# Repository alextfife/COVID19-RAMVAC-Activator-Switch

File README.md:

# COVID-AirLock

# NOTICE: There has been an issue with the tracing on these, will update once testing has been done. Transfering from kiCAD to EasyEDA removed some traces. 

Dental Office Air Filter Printed Circuit Board (PCB) Activation Switch. Inspired by the events of COVID-19.
This is a modification of a system Designed by RAMVAC Dental Vacuum System. 

<h2>Where did this come from?</h2>
A small minority of dental offices peppered around the United States in the early 2000's installed similar systems within their buildings that allow for air filtration per room, and in most cases, per 'area'. That is, it would be an inlet with 3 walls but no door, thus no closed in air source. Due to bad breath, debris from dental procedures, and sick patients, these filters were installed. 
Although its been roughly 20 years, this practice is not standard, or very popular. However that popularity is rising.

This filtration system is based almost completely on the saw dust collection filters that are installed at sawmills. However at a sawmill the power cost is astronomical due to all the vacuums being on for older systems. Newer systems use switches to activate which vacuum tubes receive suction, and to power on the vacuum.

<br>
Interestingly enough, RAMVAC produces their own switches for their current system. Theres however uses 4x the Wattage mine does. Unfortunately, my switches do not have LED's installed in the switch. 
Check theres out here: https://www.dentalez.com/product/remote-switch-panel/ 

During the COVID-19 pandemic of 2020-present, many dental offices are trying to implement this system now. 

<h2>So what is this project?</h2>
This github page is the evolution of the activator switch. The switch uses a sinusoidal signal to activate both the room's individual vacuum, and to open the aperature for that 'room's tube. 

This project is the creation of a wired switch that is more power efficient and cost efficient to produce than buy from the manufacture. 

<h2>Design Evolution</h2>
The switches are not my original design. The original design is without a patent. 
<h3>Some issues with the old, 'prototype' design. </h3>
<ol><li>It took AA batteries</li>
<li>The batteries corroded a lot and most units were switched out or bricks</li>
<li>The board itself had no seal or protection for components, and the copper on many of them was oxidizing.</li>
<li>There is no way to know when the switch had power or was dead until you took apart the switch socket.</li>
<li>The board itself is wider (by a small margin) than the footprint of the switch itself.</li>
</ol>

<h3>Design Evolution</h3>
The original design. None of this was of my doing.

With this, first thing I wanted to do was get rid of the batteries and do basic circuit analysis. 

<!--After downloading open source models of the parts I needed, I had created this. <br>
<br>-->

<br>
After checking PCB standards and compliance with the manufacturers, this was my first batch. I planned to save some money and solder them myself. <br>

<br>
Solding such small parts, and not having the funds for a microsolder meant I needed to tweak my design and send it to get fabricated and have the parts soldered on at the manufacturer. <br>
<!----><br>
To interface with the room like the old boards did, then I modified USB cables and was able to get them 5Vin as to not burn my boards.<br>
<br>

<h2>How to use it?</h2>
<h3>Connections</h3>
The boards are plugged in to the wall via USB adapter to any outlet. Therefore, you can hot switch the system around. <br>
<!---->

<br>
"Output" as seen on the board sends the signal from the board to a 2 pin terminal hardwired into the room. The "Switch" I/O on the board is where the USB power comes from. 
<h3>Usage</h3>
<br>
<i>Pictured: Dr. Robinette using vacuum tube after being activated.</i><br>
To use the airlocking vacuum system, one must simply turn it on and wait for about 10 seconds for the vacuum to charge to full sucking capacity. Then simply direct the tube to the patients breathing aperatures as shown below.<br>

<h2>Where is this?</h2>
My work as seen here is implemented at Gulf Coast Dental, in Bluewater Bay, FL. Please visit the website that I also designed! https://gulfcoastdental.com 

<br>
<i>I had express permission to photograph healthcare professionals and patients pictured to be in this documentation</i><br>

<h2>Do you want this?</h2> 
Please contact me, and I will promplty get in touch with you! 

I offered my design to the parent companyand I also applied for a position as product development engineer. I was rejected for the position. 

Under fair use, I have attached all designs and files to this repo for the unicorns out there whom this project might benefit!

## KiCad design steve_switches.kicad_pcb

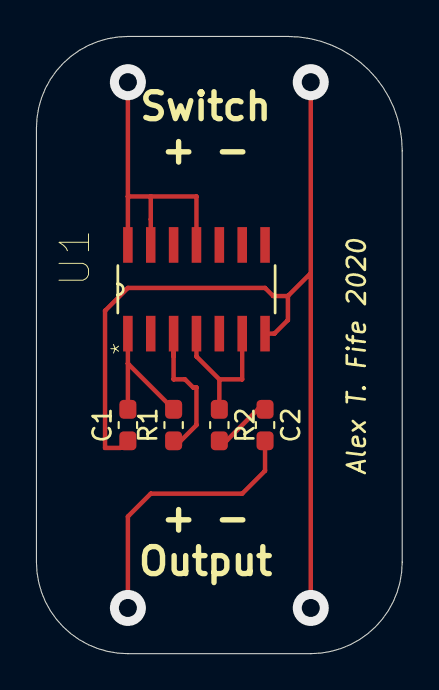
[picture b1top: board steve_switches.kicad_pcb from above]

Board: 2 copper layers, 20.3 x 34.3 mm, 5 parts (0 on the bottom side), 6 nets.

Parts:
C1: 1nF; C_0603_1608Metric_Pad1.05x0.95mm_HandSolder
C2: 120nF; C_0603_1608Metric_Pad1.05x0.95mm_HandSolder
R1: 1M; R_0603_1608Metric_Pad1.05x0.95mm_HandSolder
R2: 10k; R_0603_1608Metric_Pad1.05x0.95mm_HandSolder
U1: MC14106BDG; SOIC127P600X175-14N

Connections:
+3.3VA: U1.11, U1.13, U1.14
GND: C1.1, U1.7
unnamed: C1.2, R1.2, U1.1
unnamed: C2.1, R2.2
unnamed: R1.1, U1.3
unnamed: R2.1, U1.4, U1.6

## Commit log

2022-01-12 kiCAD open source MC14106BDG
    This wasn't created by me. I am only sharing it as part of this project
    Supports kiCAD 5.0+
2022-01-12 Add files via upload
    GBR files in a zip. Most PCB manufacturers want it this way
2022-01-12 Add files via upload
    You will need a BOM. I found it easier to go on excel and create my own based on what the manufacturer looks for. However, some may want to use this. I am supplying it here
2022-01-27 Add files via upload
    BOM
2022-06-21 The most up to date Bill of materials
